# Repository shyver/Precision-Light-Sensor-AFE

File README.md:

# Precision Photodiode Analog Front-End (AFE)

## 📌 Project Overview
This repository contains the hardware design files and LTspice simulations for a high-precision, low-noise Photodiode Signal Conditioning Board. 

Designed as a modular Analog Front-End (AFE), this board converts ambient light intensity into a clean, stable analog voltage (0–3.3V) suitable for direct sampling by microcontrollers (e.g., ESP32, STM32, Arduino) using a Transimpedance Amplifier (TIA) architecture.

## ✨ Key Features
* **Transimpedance Amplifier (TIA):** Converts microscopic photodiode currents into a measurable voltage with a calculated gain of 68kΩ.
* **Optimized Stability:** Includes a precisely calculated 20pF feedback capacitor to compensate for the photodiode's junction capacitance and prevent op-amp oscillation.
* **ADC Shock Absorption:** Features an RC low-pass output filter (100Ω + 10nF) to eliminate high-frequency noise and stabilize the signal against MCU ADC sampling glitches.
* **Ultra-Low Leakage:** Utilizes the MCP6001 CMOS operational amplifier with an input bias current of just 1pA to ensure the sensor signal is not degraded.
* **Plug-and-Play Interface:** Standard 3-pin connector (VCC, GND, OUT) for seamless integration into embedded systems.

## 🛠️ Hardware Specifications
| Component | Part / Value | Description |
| :--- | :--- | :--- |
| **Photodiode** | BPW34S | Broadband silicon photodiode. High photocurrent (~50µA at 1000 Lux), low dark current (2nA). |
| **Op-Amp** | MCP6001 | Single-supply, Rail-to-Rail Output (RRO), CMOS input (1pA Bias Current). |
| **Gain Resistor ($R_f$)** | 68 kΩ | Sets the voltage output range (Max 3.3V at ~50µA input). |
| **Compensation Cap ($C_f$)**| 20 pF | Prevents ringing/oscillation caused by the photodiode's 72pF junction capacitance. |
| **Supply Voltage** | 3.3V | Single-supply operation. Decoupled via 0.1µF capacitor. |

## 📐 Circuit Architecture & Theory

### 1. The Sensor Stage
The BPW34S photodiode is operated in photovoltaic/zero-bias mode. This configuration minimizes dark current leakage, resulting in the highest possible precision and lowest noise floor for ambient light detection.

### 2. The Transimpedance Stage
The core of the board is the TIA. The gain is set by the feedback resistor ($R_f$). 
Using Ohm's Law ($V = I \times R$), a peak ambient room light producing $~50 \mu A$ of current is multiplied by $68 k\Omega$ to produce a $~3.4V$ output, perfectly utilizing the 3.3V ADC range of modern microcontrollers.

### 3. Stability & Compensation
Photodiodes with large active areas (like the BPW34S) have high junction capacitance ($C_j \approx 72pF$). Without compensation, this capacitance creates a phase shift in the op-amp's feedback loop, causing severe ringing and instability. A 20pF feedback capacitor ($C_f$) was mathematically calculated and verified via SPICE simulation to critically damp the circuit and provide a smooth transient response.

## 📂 Repository Structure
* `/kicad` - KiCad 9.0 project files (Schematic, PCB Layout, Footprints).
* `/Simulation` - LTspice `.asc` files demonstrating Transient and AC (Frequency Response) analysis.
* `/Docs` - Datasheets for the BPW34S and MCP6001.
* `/Manufacturing` - Gerber files, Drill files, and BOM ready for PCB manufacturing (e.g., JLCPCB).
*  `/Media` - Project media and screenshots.

## 🚀 Getting Started
1. Clone this repository: `git clone https://github.com/shyver/Precision-Light-Sensor-AFE.git`
2. Open the `.pro` or `.kicad_pro` file in **KiCad**.
3. To view the simulations, open the `.asc` files located in the `/Simulation` folder using **LTspice**.

## 📝 License
This project is open-source and available under the [MIT License](LICENSE).

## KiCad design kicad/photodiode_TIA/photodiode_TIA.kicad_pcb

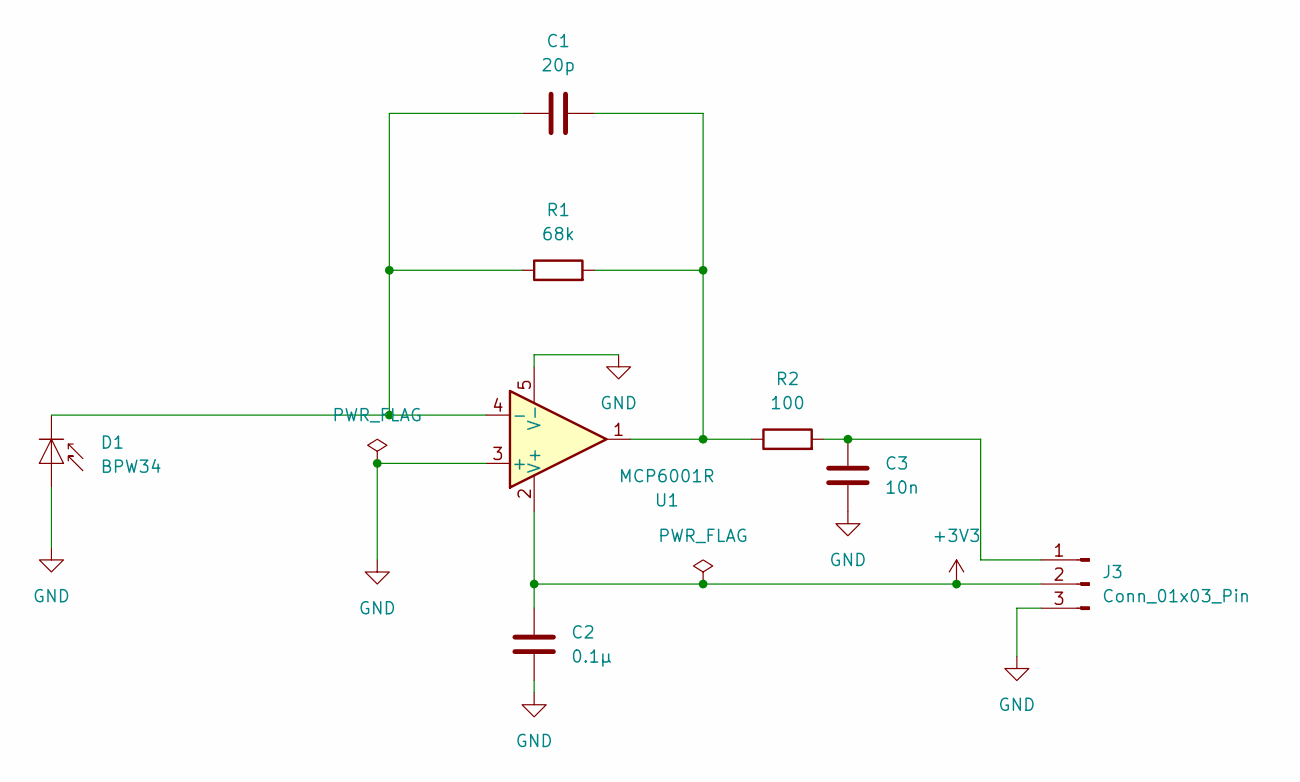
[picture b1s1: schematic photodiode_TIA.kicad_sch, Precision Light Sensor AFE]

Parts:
C1: 20p; C_0201_0603Metric
C2: 0.1µ; C_0201_0603Metric
C3: 10n; C_0201_0603Metric
D1: BPW34; Osram_DIL2_4.3x4.65mm_P5.08mm
J3: Conn_01x03_Pin; PinHeader_1x03_P2.54mm_Horizontal
R1: 68k; R_0201_0603Metric
R2: 100; R_0201_0603Metric
U1: MCP6001R; SOT-23-5

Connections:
+3V3: C2.1, J3.2, U1.2 (V+)
GND: C2.2, C3.2, D1.2 (A), J3.3, U1.3 (+), U1.5 (V-)
unnamed: C1.2, R1.2, R2.1, U1.1
unnamed: C1.1, D1.1 (K), R1.1, U1.4 (-)
unnamed: C3.1, J3.1, R2.2

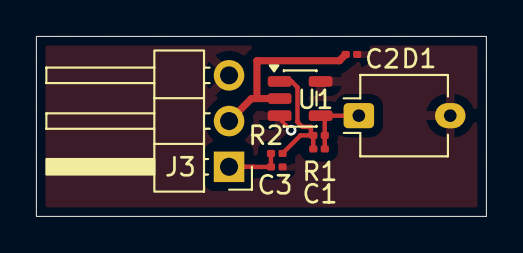
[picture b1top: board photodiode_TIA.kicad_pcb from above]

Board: 2 copper layers, 25.0 x 10.0 mm, 8 parts (0 on the bottom side), 5 nets.

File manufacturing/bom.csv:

"Reference","Qty","Value","DNP","Exclude from BOM","Exclude from Board","Footprint","Datasheet"
"C1","1","20p","","","","Capacitor_SMD:C_0201_0603Metric","~"
"C2","1","0.1µ","","","","Capacitor_SMD:C_0201_0603Metric","~"
"C3","1","10n","","","","Capacitor_SMD:C_0201_0603Metric","~"
"D1","1","BPW34","","","","OptoDevice:Osram_DIL2_4.3x4.65mm_P5.08mm","http://www.vishay.com/docs/81521/bpw34.pdf"
"J3","1","Conn_01x03_Pin","","","","Connector_PinHeader_2.54mm:PinHeader_1x03_P2.54mm_Horizontal","~"
"R1","1","68k","","","","Resistor_SMD:R_0201_0603Metric","~"
"R2","1","100","","","","Resistor_SMD:R_0201_0603Metric","~"
"U1","1","MCP6001R","","","","Package_TO_SOT_SMD:SOT-23-5","https://ww1.microchip.com/downloads/en/DeviceDoc/MCP6001-1R-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"

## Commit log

2026-03-22 first commit, schematic ready
2026-03-22 reorganized rpeo
2026-03-22 complete layout
2026-03-22 added media
2026-03-22 added manufacturing files
2026-03-22 Add README for Precision Photodiode AFE project
    Added detailed project overview, features, specifications, and instructions for the Precision Photodiode Analog Front-End (AFE).
2026-03-22 Update KiCad version in README
2026-03-22 Add 3D PCB screenshot to README
    Updated README to include a 3D PCB screenshot.
2026-03-22 Add MIT License to the project

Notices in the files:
README.md:
License: MIT
